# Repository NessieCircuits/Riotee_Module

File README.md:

# Riotee Module Hardware Design Files

The Riotee Module is a stamp-sized unit (27.2mm by 15.2mm) that can be soldered onto a user's \ac{pcb} with additional circuitry like sensors or harvesters to create deployment-ready battery-free devices quickly.
It integrates harvesting circuitry, two MCUs, an RTC, a PCB antenna, and an LED on a compact 4-layer PCB enclosed in a metal RF shield.
The module features breadboard-compatible castellated holes exposing essential signals, including 11 GPIO, two of which can also function as analog inputs.
Four additional signals on the back of the module are available when reflow-soldered onto a carrier board.

For more details and pinouts, refer to the [documentation](https://www.riotee.nessie-circuits.de/docs/latest/hardware/module.html).

Latest design files:
 - [Schematics](https://www.riotee.nessie-circuits.de/artifacts/module/latest/schematics.pdf)
 - [Layout](https://www.riotee.nessie-circuits.de/artifacts/module/latest/pcb.pdf)
 - [3D rendering](https://www.riotee.nessie-circuits.de/artifacts/module/latest/3drendering.png)
 - [Gerber](https://www.riotee.nessie-circuits.de/artifacts/module/latest/gerber.zip)
 - [BOM](https://www.riotee.nessie-circuits.de/artifacts/module/latest/bom.csv)
 - [3D step model](./resources/RioteeModule.step)
 - [Kicad schematic symbol](./resources/RioteeModule.kicad_sym)
 - [Kicad footprint](./resources/RioteeModule.pretty)

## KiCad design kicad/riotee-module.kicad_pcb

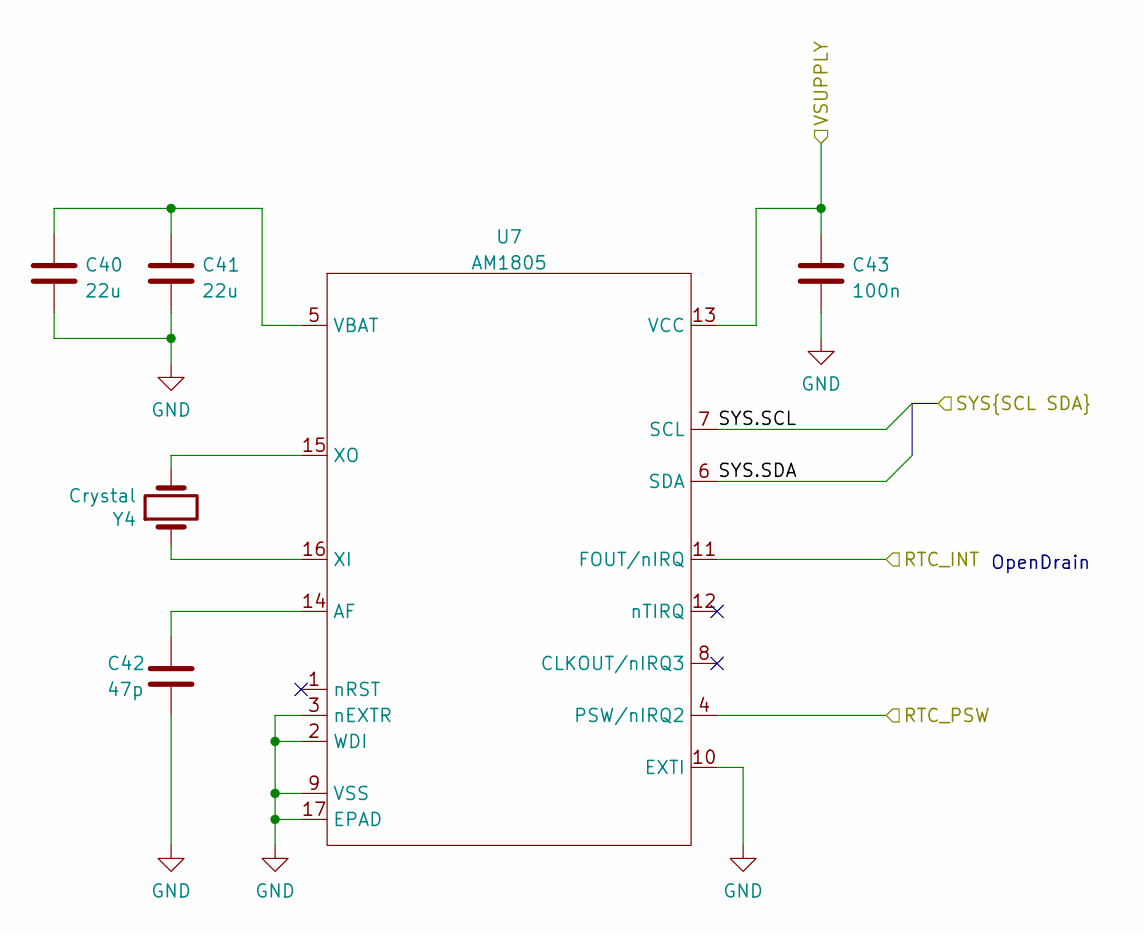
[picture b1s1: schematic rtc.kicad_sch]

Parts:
C40, C41: 22u; C_0402_1005Metric; MPN GRM158R61A226ME15D
C42: 47p; C_0201_0603Metric; MPN CC0201JRNPO9BN470
C43: 100n; C_0201_0603Metric; MPN GRM033R61A104ME15D
U7: AM1805; AM_QFN16; MPN AM1805
Y4: Crystal; ECX-12R; MPN CM8V-T1A-32.768KHZ-9PF-20PPM-TA-QC

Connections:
/Board Connectors/SYS.SCL: U7.7 (SCL); also elsewhere on the board
/Board Connectors/SYS.SDA: U7.6 (SDA); also elsewhere on the board
/Board Connectors/VSHUNT: C43.1, U7.13 (VCC); also elsewhere on the board
/MSP430FR/RTC_INT: U7.11 (FOUT/nIRQ); also elsewhere on the board
/Power Supply/RTC_PSW: U7.4 (PSW/nIRQ2); also elsewhere on the board
GND: C40.2, C41.2, C42.2, C43.2, U7.2 (WDI), U7.3 (nEXTR), U7.9 (VSS), U7.10 (EXTI), U7.17 (EPAD); also elsewhere on the board
unnamed: C42.1, U7.14 (AF)
unnamed: C40.1, C41.1, U7.5 (VBAT)
unnamed: U7.16 (XI), Y4.1
unnamed: U7.15 (XO), Y4.2

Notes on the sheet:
OpenDrain

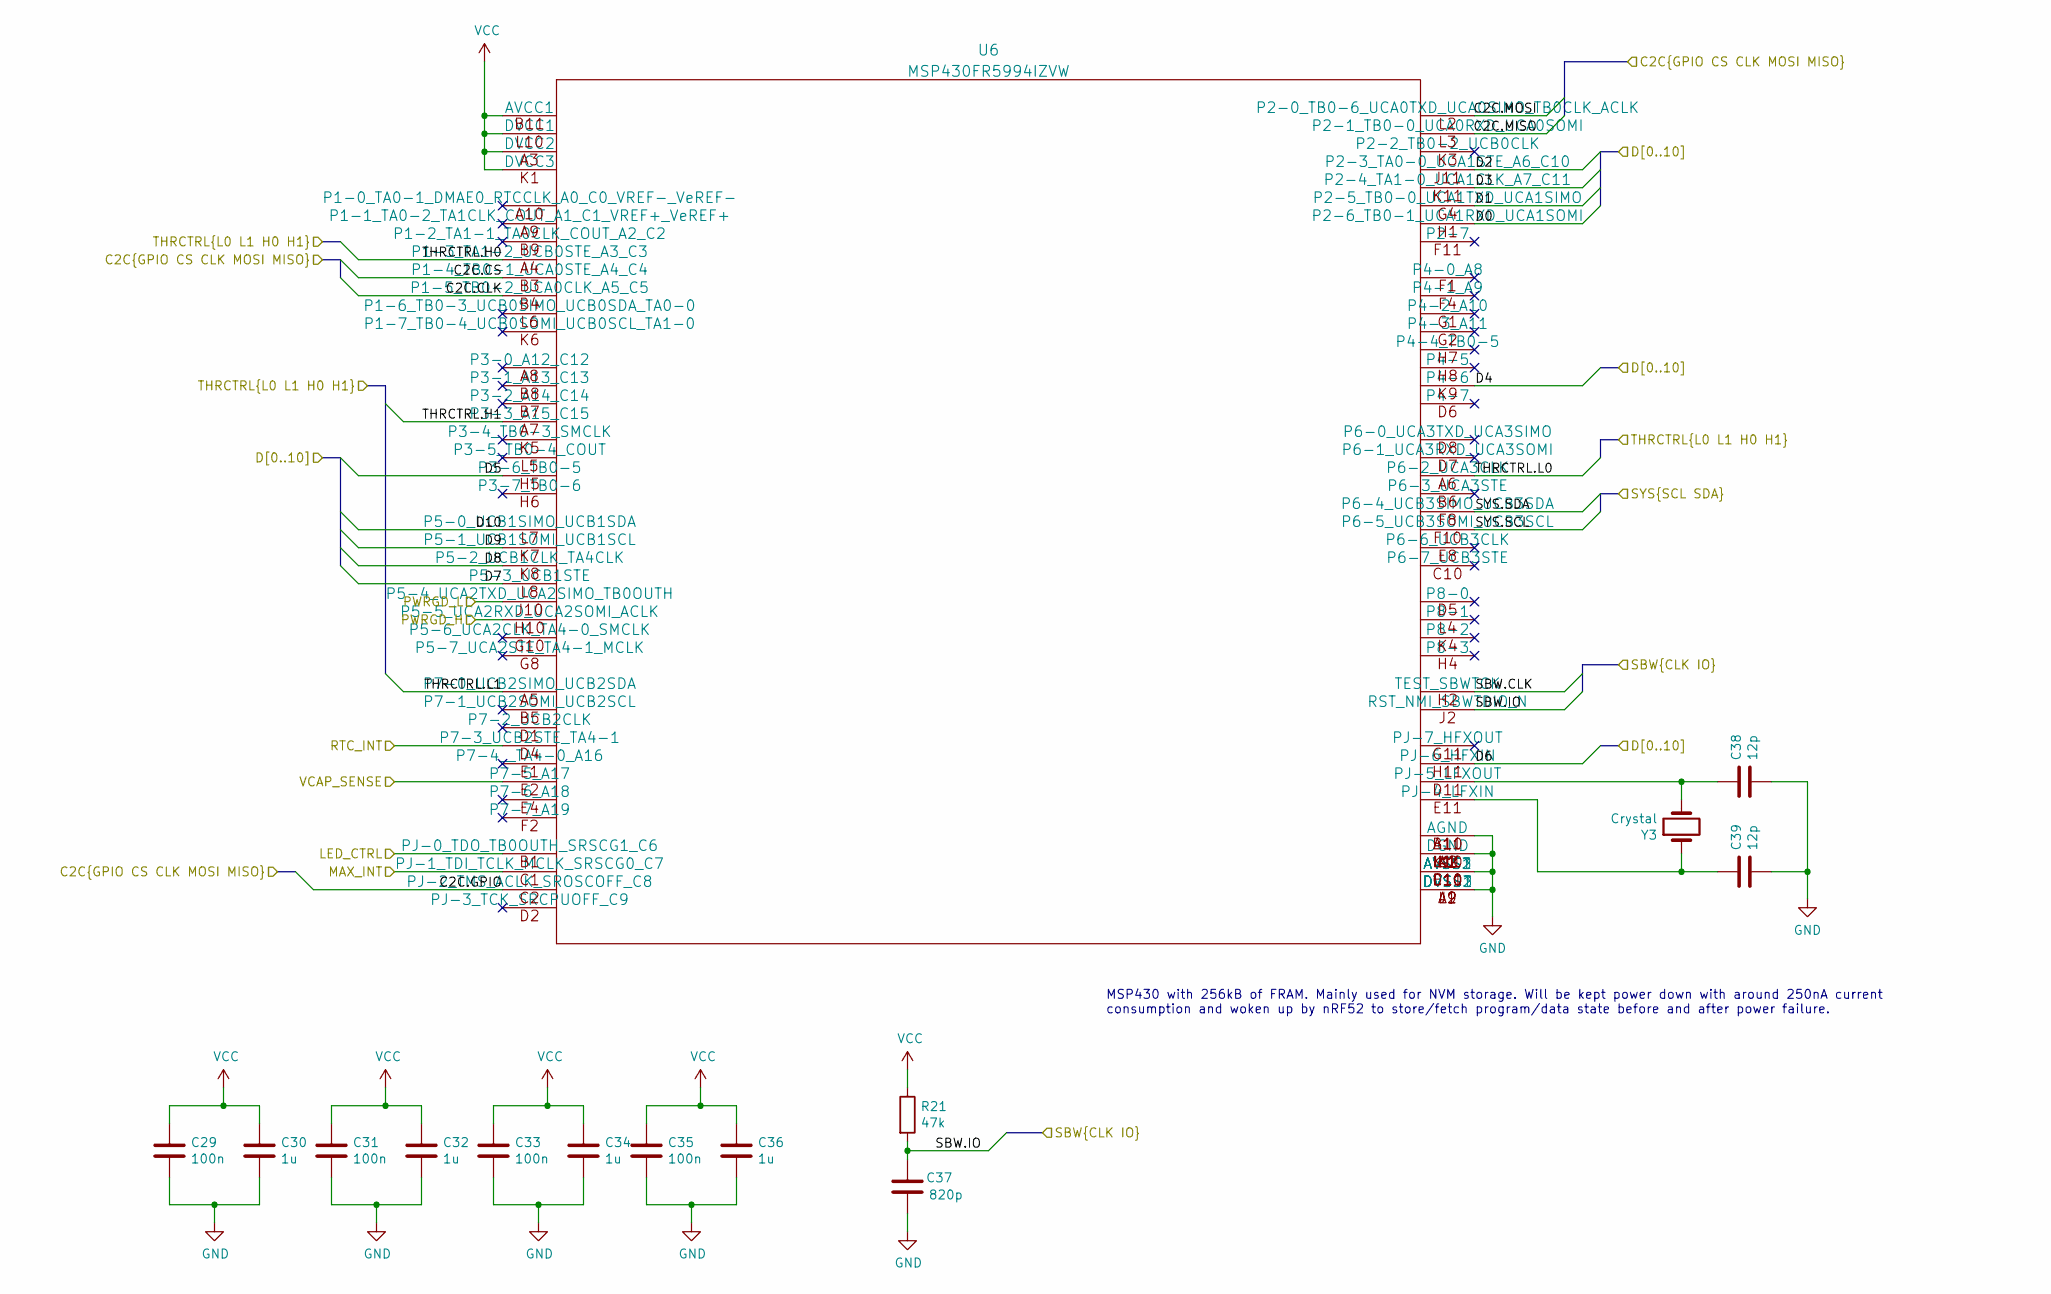
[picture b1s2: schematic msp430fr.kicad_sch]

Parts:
C29, C31, C33, C35: 100n; C_0201_0603Metric; MPN GRM033R61A104ME15D
C30, C32, C34, C36: 1u; C_0201_0603Metric; MPN GRM033R61C105ME15D
C37: 820p; C_0201_0603Metric; MPN GRM0335C1H821JE01D
C38, C39: 12p; C_0201_0603Metric; MPN GRM0335C1H120GA01D
R21: 47k; R_0201_0603Metric; MPN RC0201FR-0747KL
U6: MSP430FR5994IZVW; TI_ZVW; MPN MSP430FR5994IZVW
Y3: Crystal; ECX-12R; MPN CM8V-T1A-32.768KHZ-9PF-20PPM-TA-QC

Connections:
/Board Connectors/D0: U6.H1 (P2-6_TB0-1_UCA1RXD_UCA1SOMI); also elsewhere on the board
/Board Connectors/D1: U6.G4 (P2-5_TB0-0_UCA1TXD_UCA1SIMO); also elsewhere on the board
/Board Connectors/D2: U6.J11 (P2-3_TA0-0_UCA1STE_A6_C10); also elsewhere on the board
/Board Connectors/D3: U6.K11 (P2-4_TA1-0_UCA1CLK_A7_C11); also elsewhere on the board
/Board Connectors/D4: U6.K9 (P4-6); also elsewhere on the board
/Board Connectors/D5: U6.H5 (P3-6_TB0-5); also elsewhere on the board
/Board Connectors/D6: U6.H11 (PJ-6_HFXIN); also elsewhere on the board
/Board Connectors/D7: U6.L8 (P5-3_UCB1STE); also elsewhere on the board
/Board Connectors/D8: U6.K8 (P5-2_UCB1CLK_TA4CLK); also elsewhere on the board
/Board Connectors/D9: U6.K7 (P5-1_UCB1SOMI_UCB1SCL); also elsewhere on the board
/Board Connectors/D10: U6.L7 (P5-0_UCB1SIMO_UCB1SDA); also elsewhere on the board
/Board Connectors/LED_CTRL: U6.B1 (PJ-0_TDO_TB0OUTH_SRSCG1_C6); also elsewhere on the board
/Board Connectors/SBW.CLK: U6.H2 (TEST_SBWTCK); also elsewhere on the board
/Board Connectors/SBW.IO: C37.1, R21.2, U6.J2 (RST_NMI_SBWTDIO_N); also elsewhere on the board
/Board Connectors/SYS.SCL: U6.F10 (P6-5_UCB3SOMI_UCB3SCL); also elsewhere on the board
/Board Connectors/SYS.SDA: U6.F8 (P6-4_UCB3SIMO_UCB3SDA); also elsewhere on the board
/Board Connectors/VCAP_SENSE: U6.E2 (P7-5_A17); also elsewhere on the board
/Energy Management/PWRGD_H: U6.H10 (P5-5_UCA2RXD_UCA2SOMI_ACLK); also elsewhere on the board
/Energy Management/PWRGD_L: U6.J10 (P5-4_UCA2TXD_UCA2SIMO_TB0OUTH); also elsewhere on the board
/Energy Management/THRCTRL.H0: U6.A4 (P1-3_TA1-2_UCB0STE_A3_C3); also elsewhere on the board
/Energy Management/THRCTRL.H1: U6.A7 (P3-3_A15_C15); also elsewhere on the board
/Energy Management/THRCTRL.L0: U6.A6 (P6-2_UCA3CLK); also elsewhere on the board
/Energy Management/THRCTRL.L1: U6.A5 (P7-0_UCB2SIMO_UCB2SDA); also elsewhere on the board
/MSP430FR/C2C.CLK: U6.B4 (P1-5_TB0-2_UCA0CLK_A5_C5); also elsewhere on the board
/MSP430FR/C2C.CS: U6.B3 (P1-4_TB0-1_UCA0STE_A4_C4); also elsewhere on the board
/MSP430FR/C2C.GPIO: U6.C2 (PJ-2_TMS_ACLK_SROSCOFF_C8); also elsewhere on the board
/MSP430FR/C2C.MISO: U6.L3 (P2-1_TB0-0_UCA0RXD_UCA0SOMI); also elsewhere on the board
/MSP430FR/C2C.MOSI: U6.L2 (P2-0_TB0-6_UCA0TXD_UCA0SIMO_TB0CLK_ACLK); also elsewhere on the board
/MSP430FR/MAX_INT: U6.C1 (PJ-1_TDI_TCLK_MCLK_SRSCG0_C7); also elsewhere on the board
/MSP430FR/RTC_INT: U6.D4 (P7-3_UCB2STE_TA4-1); also elsewhere on the board
GND: C29.2, C30.2, C31.2, C32.2, C33.2, C34.2, C35.2, C36.2, C37.2, C38.2, C39.2, U6.A1 (DGND), U6.A2 (DVSS2), U6.A11 (AGND), U6.B10 (AGND), U6.C11 (AVSS1), U6.D10 (AVSS2), U6.E10 (AVSS3), U6.J1 (DVSS3), U6.K2 (DGND), U6.K10 (DGND), U6.L1 (DGND), U6.L9 (DVSS1), U6.L11 (DGND); also elsewhere on the board
unnamed: C39.1, U6.E11 (PJ-4_LFXIN), Y3.1
unnamed: C38.1, U6.D11 (PJ-5_LFXOUT), Y3.2
VCC: C29.1, C30.1, C31.1, C32.1, C33.1, C34.1, C35.1, C36.1, R21.1, U6.A3 (DVCC2), U6.B11 (AVCC1), U6.K1 (DVCC3), U6.L10 (DVCC1); also elsewhere on the board

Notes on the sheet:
MSP430 with 256kB of FRAM. Mainly used for NVM storage. Will be kept power down with around 250nA current consumption and woken up by nRF52 to store/fetch program/data state before and after power failure.

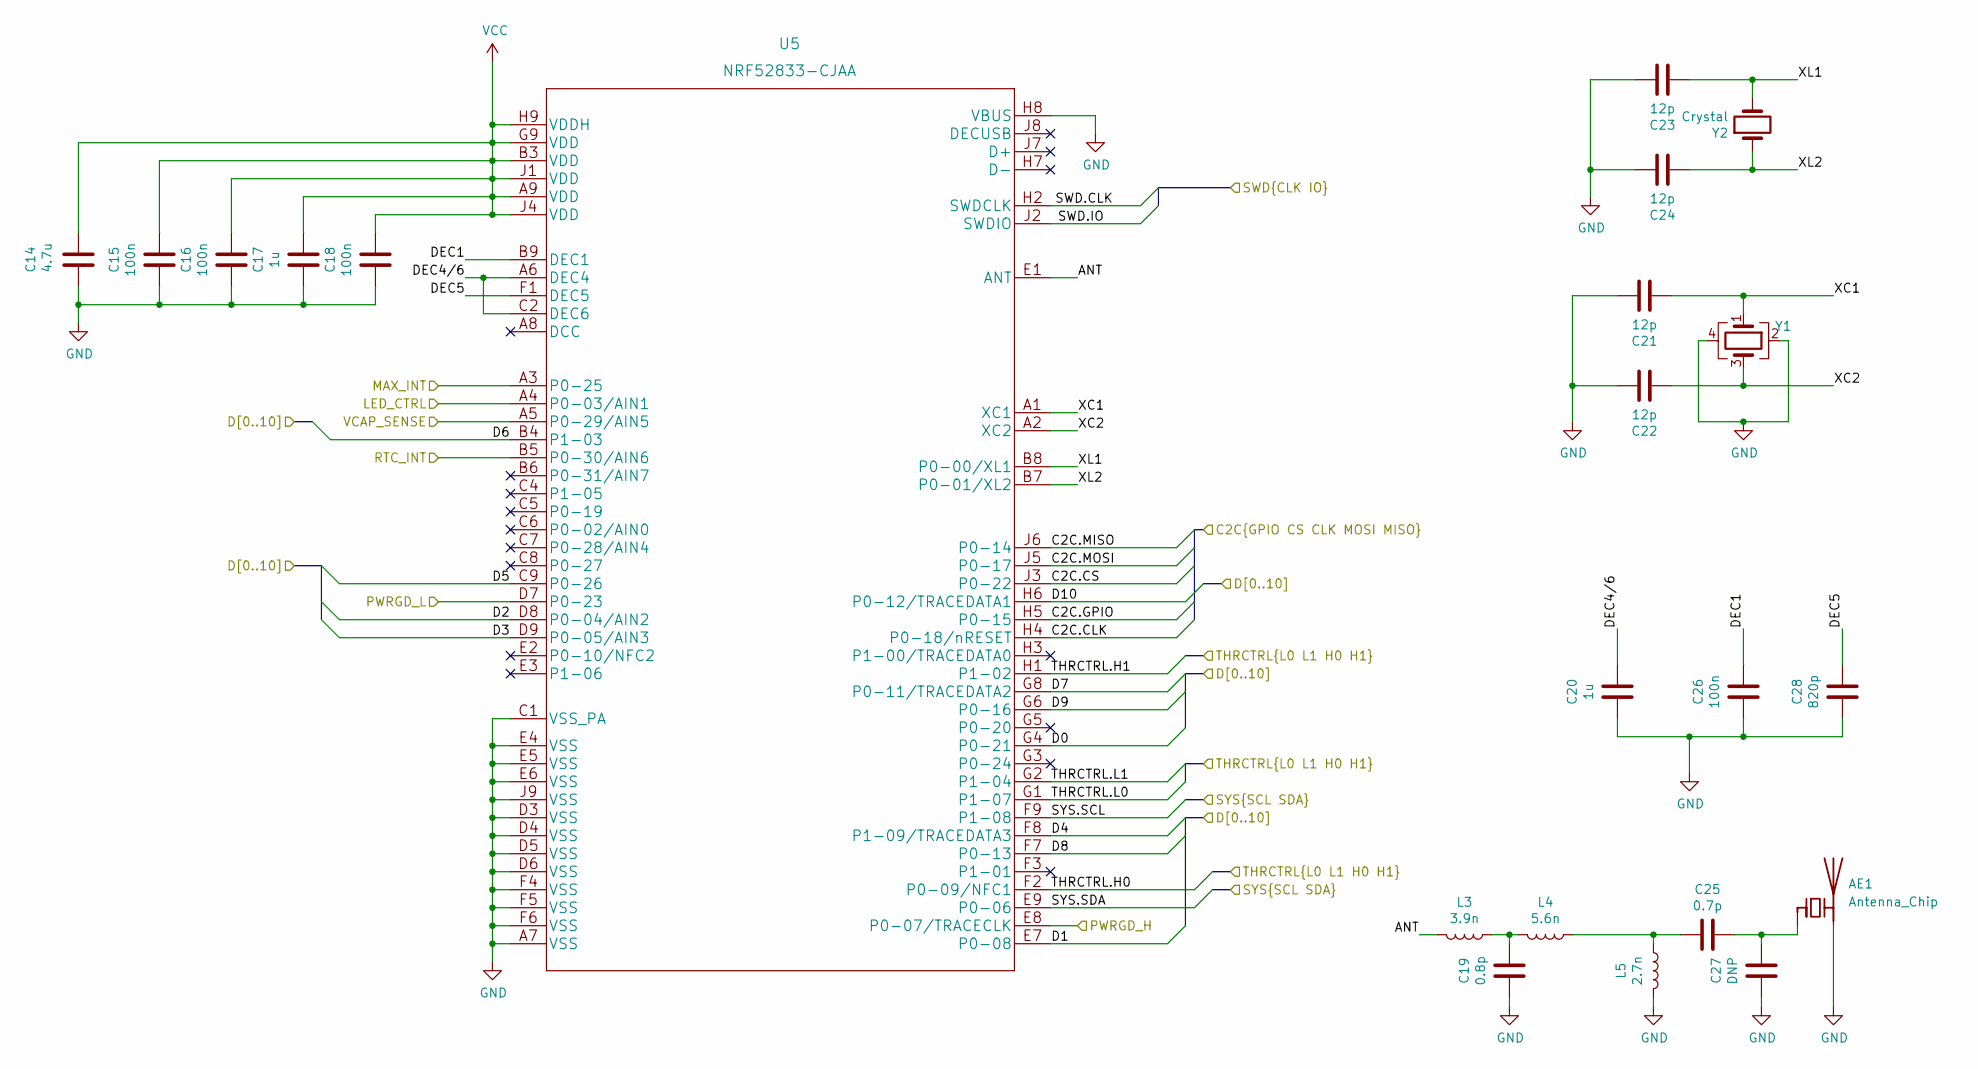
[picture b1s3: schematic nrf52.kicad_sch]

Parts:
AE1: Antenna_Chip; Texas_SWRA117D_2.4GHz_Left
C14: 4.7u; C_0402_1005Metric; MPN CL05A475MP5NRNC
C15, C16, C18, C26: 100n; C_0201_0603Metric; MPN GRM033R61A104ME15D
C17, C20: 1u; C_0201_0603Metric; MPN GRM033R61C105ME15D
C19: 0.8p; RFSMD_0201_0603Metric; MPN GRT0335C1HR80WA02D
C21, C22, C23, C24: 12p; C_0201_0603Metric; MPN GRM0335C1H120GA01D
C25: 0.7p; RFSMD_0201_0603Metric; MPN GRM0335C1HR70WA01D
C27: DNP; RFSMD_0201_0603Metric
C28: 820p; C_0201_0603Metric; MPN GRM0335C1H821JE01D
L3: 3.9n; RFSMD_0201_0603Metric; MPN LQP03TN3N9B02D
L4: 5.6n; RFSMD_0201_0603Metric; MPN LQP03TN5N6J02D
L5: 2.7n; RFSMD_0201_0603Metric; MPN LQP03TN2N7B02D
U5: NRF52833-CJAA; MPN NRF52833-CJAA
Y1: ECS-320-8-47B-7KM-TR; ECS_ECX-1247B; MPN ECS-320-CDX-2152
Y2: Crystal; ECX-12R; MPN CM8V-T1A-32.768KHZ-9PF-20PPM-TA-QC

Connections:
/Board Connectors/D0: U5.G4 (P0-21); also elsewhere on the board
/Board Connectors/D1: U5.E7 (P0-08); also elsewhere on the board
/Board Connectors/D2: U5.D8 (P0-04/AIN2); also elsewhere on the board
/Board Connectors/D3: U5.D9 (P0-05/AIN3); also elsewhere on the board
/Board Connectors/D4: U5.F8 (P1-09/TRACEDATA3); also elsewhere on the board
/Board Connectors/D5: U5.C9 (P0-26); also elsewhere on the board
/Board Connectors/D6: U5.B4 (P1-03); also elsewhere on the board
/Board Connectors/D7: U5.G8 (P0-11/TRACEDATA2); also elsewhere on the board
/Board Connectors/D8: U5.F7 (P0-13); also elsewhere on the board
/Board Connectors/D9: U5.G6 (P0-16); also elsewhere on the board
/Board Connectors/D10: U5.H6 (P0-12/TRACEDATA1); also elsewhere on the board
/Board Connectors/LED_CTRL: U5.A4 (P0-03/AIN1); also elsewhere on the board
/Board Connectors/SWD.CLK: U5.H2 (SWDCLK); also elsewhere on the board
/Board Connectors/SWD.IO: U5.J2 (SWDIO); also elsewhere on the board
/Board Connectors/SYS.SCL: U5.F9 (P1-08); also elsewhere on the board
/Board Connectors/SYS.SDA: U5.E9 (P0-06); also elsewhere on the board
/Board Connectors/VCAP_SENSE: U5.A5 (P0-29/AIN5); also elsewhere on the board
/Energy Management/PWRGD_H: U5.E8 (P0-07/TRACECLK); also elsewhere on the board
/Energy Management/PWRGD_L: U5.D7 (P0-23); also elsewhere on the board
/Energy Management/THRCTRL.H0: U5.F2 (P0-09/NFC1); also elsewhere on the board
/Energy Management/THRCTRL.H1: U5.H1 (P1-02); also elsewhere on the board
/Energy Management/THRCTRL.L0: U5.G1 (P1-07); also elsewhere on the board
/Energy Management/THRCTRL.L1: U5.G2 (P1-04); also elsewhere on the board
/MSP430FR/C2C.CLK: U5.H4 (P0-18/nRESET); also elsewhere on the board
/MSP430FR/C2C.CS: U5.J3 (P0-22); also elsewhere on the board
/MSP430FR/C2C.GPIO: U5.H5 (P0-15); also elsewhere on the board
/MSP430FR/C2C.MISO: U5.J6 (P0-14); also elsewhere on the board
/MSP430FR/C2C.MOSI: U5.J5 (P0-17); also elsewhere on the board
/MSP430FR/MAX_INT: U5.A3 (P0-25); also elsewhere on the board
/MSP430FR/RTC_INT: U5.B5 (P0-30/AIN6); also elsewhere on the board
/nRF52/ANT: L3.2, U5.E1 (ANT)
/nRF52/DEC1: C26.2, U5.B9 (DEC1)
/nRF52/DEC4/6: C20.2, U5.A6 (DEC4), U5.C2 (DEC6)
/nRF52/DEC5: C28.2, U5.F1 (DEC5)
/nRF52/XC1: C21.1, U5.A1 (XC1), Y1.1
/nRF52/XC2: C22.1, U5.A2 (XC2), Y1.3
/nRF52/XL1: C23.1, U5.B8 (P0-00/XL1), Y2.2
/nRF52/XL2: C24.1, U5.B7 (P0-01/XL2), Y2.1
GND: AE1.2 (PCB_Trace), C14.2, C15.1, C16.1, C17.1, C18.1, C19.1, C20.1, C21.2, C22.2, C23.2, C24.2, C26.1, C27.1, C28.1, L5.2, U5.A7 (VSS), U5.C1 (VSS_PA), U5.D3 (VSS), U5.D4 (VSS), U5.D5 (VSS), U5.D6 (VSS), U5.E4 (VSS), U5.E5 (VSS), U5.E6 (VSS), U5.F4 (VSS), U5.F5 (VSS), U5.F6 (VSS), U5.H8 (VBUS), U5.J9 (VSS), Y1.2, Y1.4; also elsewhere on the board
unnamed: AE1.1 (FEED), C25.2, C27.2
unnamed: C19.2, L3.1, L4.2
unnamed: C25.1, L4.1, L5.1
VCC: C14.1, C15.2, C16.2, C17.2, C18.2, U5.A9 (VDD), U5.B3 (VDD), U5.G9 (VDD), U5.H9 (VDDH), U5.J1 (VDD), U5.J4 (VDD); also elsewhere on the board

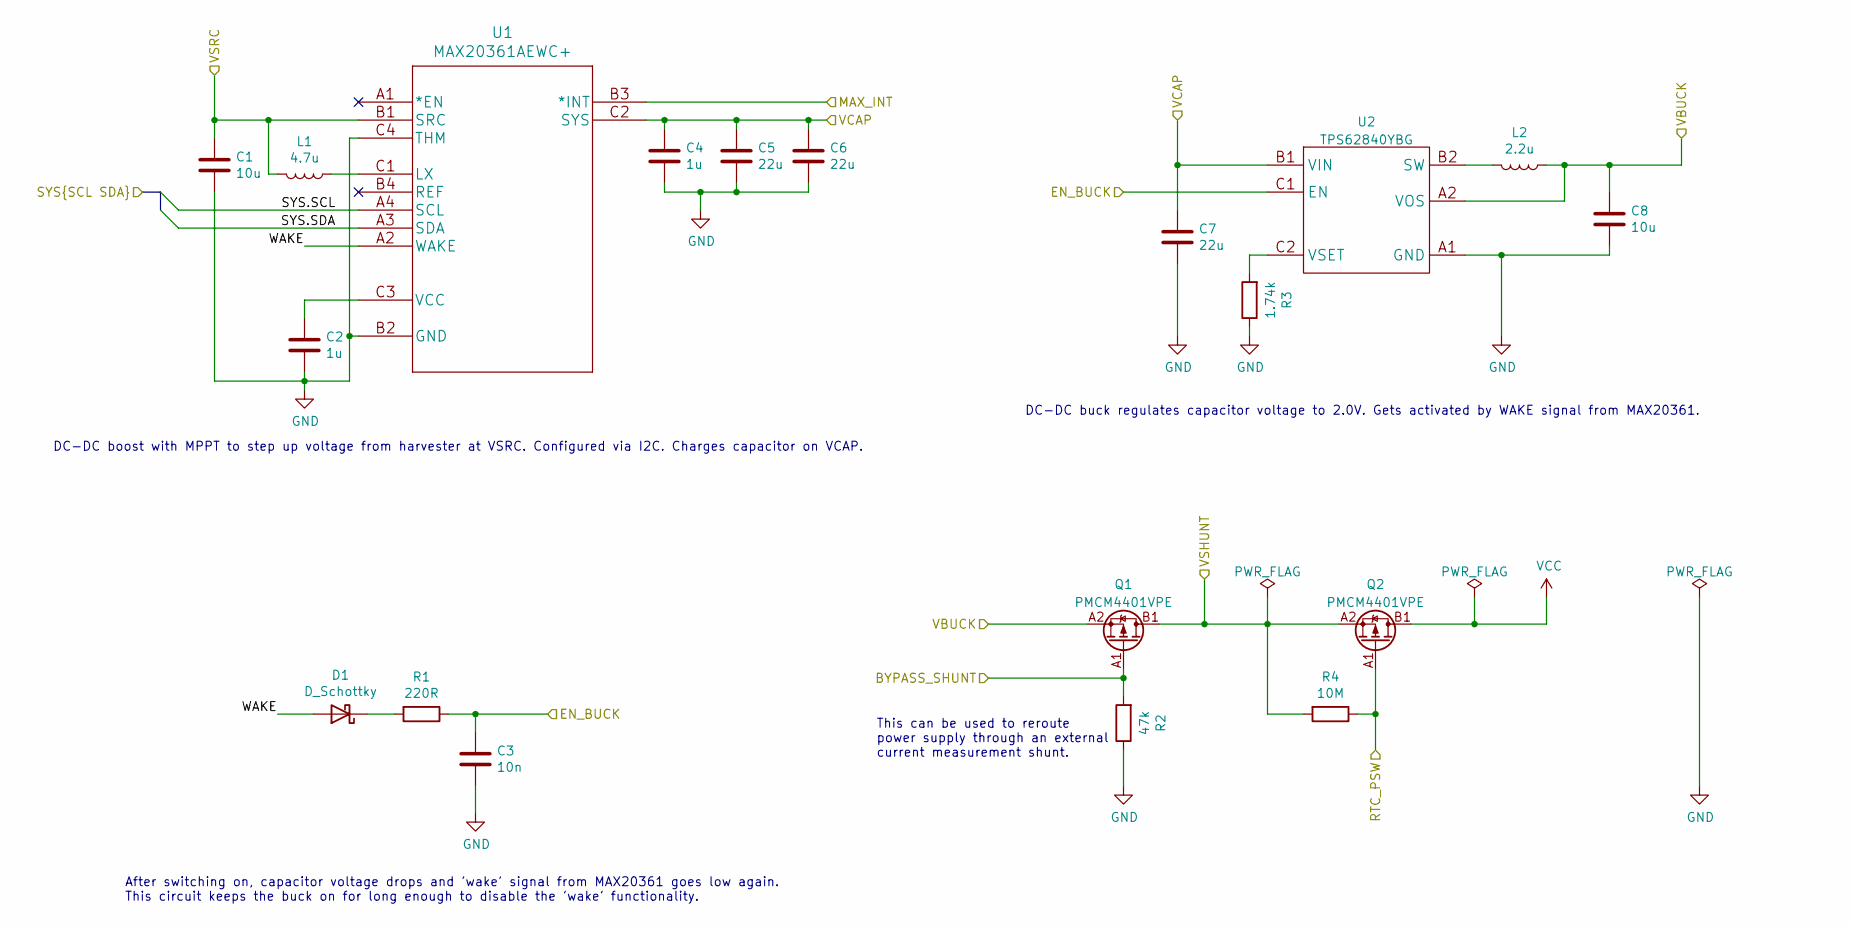
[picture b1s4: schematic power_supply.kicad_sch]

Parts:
C1, C8: 10u; C_0402_1005Metric; MPN GRM155R61A106ME11D
C2, C4: 1u; C_0201_0603Metric; MPN GRM033R61C105ME15D
C3: 10n; C_0201_0603Metric; MPN GRM033R61A103KA01D
C5, C6, C7: 22u; C_0402_1005Metric; MPN GRM158R61A226ME15D
D1: D_Schottky; D_0402_1005Metric; MPN CDBQR0130R
L1: 4.7u; L_0805_2012Metric; MPN MLZ2012N4R7LTD25
L2: 2.2u; L_0603_1608Metric; MPN MLZ1608N2R2LT000
Q1, Q2: PMCM4401VPE; NXP_WLCSP4; MPN PMCM4401VPEZ
R1: 220R; R_0201_0603Metric; MPN RC0201FR-07220RL
R2: 47k; R_0201_0603Metric; MPN RC0201FR-0747KL
R3: 1.74k; R_0201_0603Metric; MPN RC0201FR-071K74L
R4: 10M; R_0201_0603Metric; MPN RC0201FR-0710ML
U1: MAX20361AEWC+; MX_W121C1+2; MPN MAX20361AEWC+
U2: TPS62840YBG; TI_YBG6; MPN TPS62840YBG

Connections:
/Board Connectors/BYPASS_SHUNT: Q1.A1 (G), R2.2; also elsewhere on the board
/Board Connectors/EN_BUCK: C3.1, R1.1, U2.C1 (EN); also elsewhere on the board
/Board Connectors/SYS.SCL: U1.A4 (SCL); also elsewhere on the board
/Board Connectors/SYS.SDA: U1.A3 (SDA); also elsewhere on the board
/Board Connectors/VBUCK: C8.1, L2.1, Q1.A2 (S), U2.A2 (VOS); also elsewhere on the board
/Board Connectors/VCAP: C4.1, C5.1, C6.1, C7.1, U1.C2 (SYS), U2.B1 (VIN); also elsewhere on the board
/Board Connectors/VSHUNT: Q1.B1 (D), Q2.A2 (S), R4.2; also elsewhere on the board
/Board Connectors/VSRC: C1.1, L1.2, U1.B1 (SRC); also elsewhere on the board
/MSP430FR/MAX_INT: U1.B3 (*INT); also elsewhere on the board
/Power Supply/RTC_PSW: Q2.A1 (G), R4.1; also elsewhere on the board
/Power Supply/WAKE: D1.2 (A), U1.A2 (WAKE)
GND: C1.2, C2.2, C3.2, C4.2, C5.2, C6.2, C7.2, C8.2, R2.1, R3.1, U1.B2 (GND), U1.C4 (THM), U2.A1 (GND); also elsewhere on the board
unnamed: D1.1 (K), R1.2
unnamed: L1.1, U1.C1 (LX)
unnamed: C2.1, U1.C3 (VCC)
unnamed: L2.2, U2.B2 (SW)
unnamed: R3.2, U2.C2 (VSET)
VCC: Q2.B1 (D); also elsewhere on the board

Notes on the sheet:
After switching on, capacitor voltage drops and 'wake' signal from MAX20361 goes low again. This circuit keeps the buck on for long enough to disable the 'wake' functionality.
This can be used to reroute power supply through an external current measurement shunt.
DC-DC boost with MPPT to step up voltage from harvester at VSRC. Configured via I2C. Charges capacitor on VCAP.
DC-DC buck regulates capacitor voltage to 2.0V. Gets activated by WAKE signal from MAX20361.

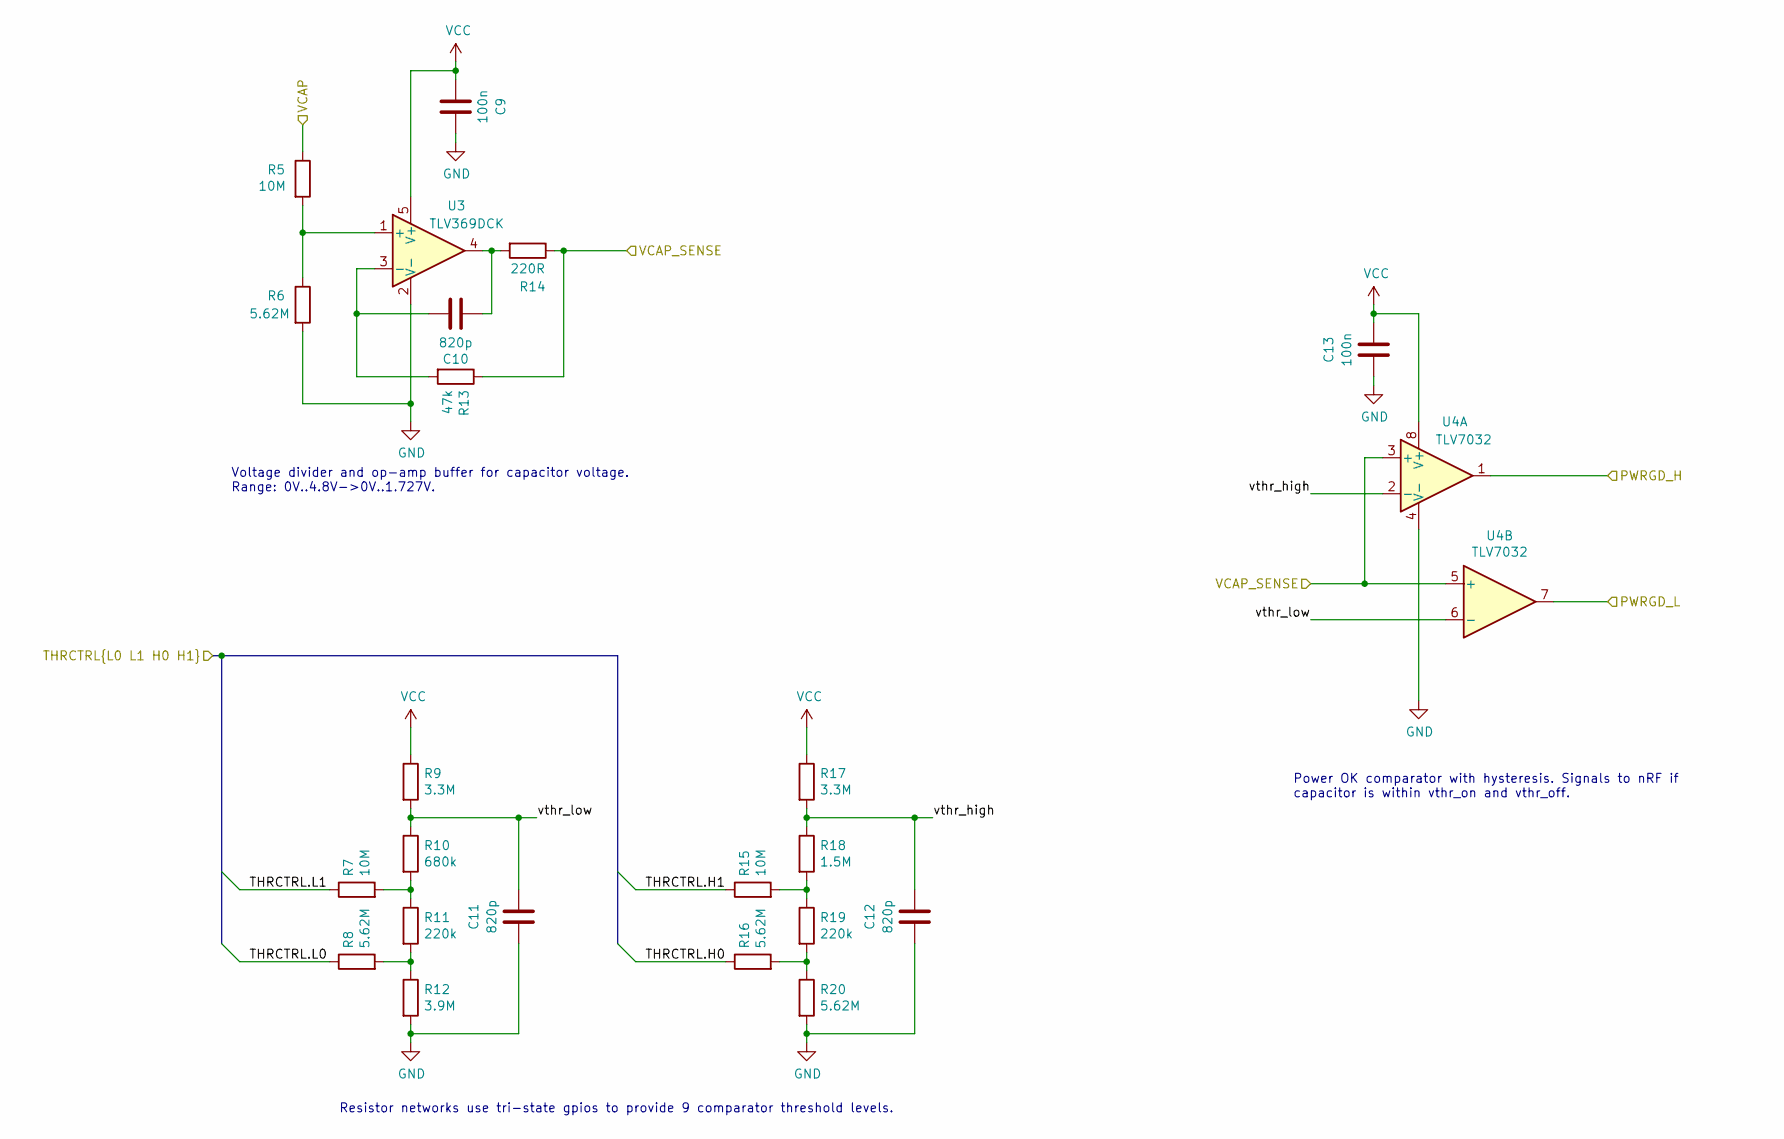
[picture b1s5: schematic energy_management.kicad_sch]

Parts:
C9, C13: 100n; C_0201_0603Metric; MPN GRM033R61A104ME15D
C10, C11, C12: 820p; C_0201_0603Metric; MPN GRM0335C1H821JE01D
R5, R7, R15: 10M; R_0201_0603Metric; MPN RC0201FR-0710ML
R6, R8, R16, R20: 5.62M; R_0201_0603Metric; MPN RC0201FR-075M62L
R9, R17: 3.3M; R_0201_0603Metric; MPN RC0201FR-073M3L
R10: 680k; R_0201_0603Metric; MPN RC0201FR-07680KL
R11, R19: 220k; R_0201_0603Metric; MPN RC0201FR-07220KL
R12: 3.9M; R_0201_0603Metric; MPN RC0201FR-073M9L
R13: 47k; R_0201_0603Metric; MPN RC0201FR-0747KL
R14: 220R; R_0201_0603Metric; MPN RC0201FR-07220RL
R18: 1.5M; R_0201_0603Metric; MPN RC0201FR-071M5L
U3: TLV369DCK; TI_SC70-5_DCK5; MPN TLV369IDCK
U4: TLV7032; TI_WSON8_DSG; MPN TLV7032DSG

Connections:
/Board Connectors/VCAP: R5.1; also elsewhere on the board
/Board Connectors/VCAP_SENSE: R13.1, R14.1, U4.3 (+), U4.5 (+); also elsewhere on the board
/Energy Management/PWRGD_H: U4.1; also elsewhere on the board
/Energy Management/PWRGD_L: U4.7; also elsewhere on the board
/Energy Management/THRCTRL.H0: R16.1; also elsewhere on the board
/Energy Management/THRCTRL.H1: R15.1; also elsewhere on the board
/Energy Management/THRCTRL.L0: R8.1; also elsewhere on the board
/Energy Management/THRCTRL.L1: R7.1; also elsewhere on the board
/Energy Management/vthr_high: C12.2, R17.2, R18.1, U4.2 (-)
/Energy Management/vthr_low: C11.2, R9.2, R10.1, U4.6 (-)
GND: C9.1, C11.1, C12.1, C13.1, R6.2, R12.2, R20.2, U3.2 (V-), U4.4 (V-), U4.9 (THM); also elsewhere on the board
unnamed: C10.1, R14.2, U3.4
unnamed: R7.2, R10.2, R11.1
unnamed: R8.2, R11.2, R12.1
unnamed: R15.2, R18.2, R19.1
unnamed: R16.2, R19.2, R20.1
unnamed: R5.2, R6.1, U3.1 (+)
unnamed: C10.2, R13.2, U3.3 (-)
VCC: C9.2, C13.2, R9.1, R17.1, U3.5 (V+), U4.8 (V+); also elsewhere on the board

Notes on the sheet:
Power OK comparator with hysteresis. Signals to nRF if capacitor is within vthr_on and vthr_off.
Resistor networks use tri-state gpios to provide 9 comparator threshold levels.
Voltage divider and op-amp buffer for capacitor voltage. Range: 0V..4.8V->0V..1.727V.

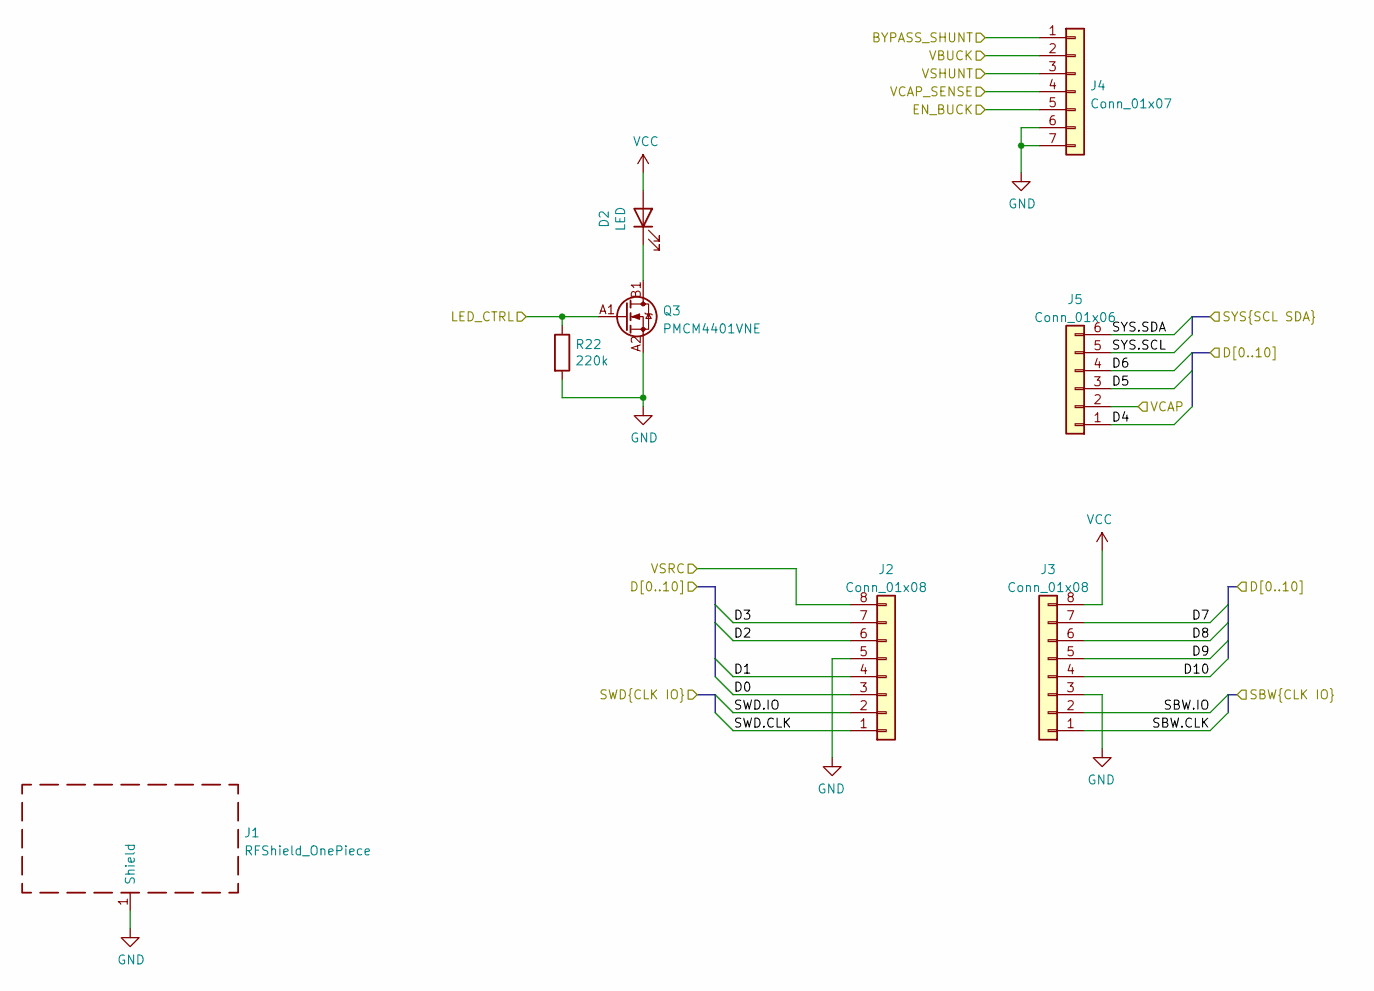
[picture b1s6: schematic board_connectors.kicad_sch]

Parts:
D2: LED; LED_0402_1005Metric; MPN 5988A20107F
J1: RFShield_OnePiece; EMI_SHIELD_CSTM
J2: Conn_01x08; CastellatedHoles_1x08_P2.54mm_Left
J3: Conn_01x08; CastellatedHoles_1x08_P2.54mm_Right
J4: Conn_01x07; BackPads
J5: Conn_01x06; CastellatedHoles_1x06_P2.54mm
Q3: PMCM4401VNE; NXP_WLCSP4; MPN PMCM4401VNEAZ
R22: 220k; R_0201_0603Metric; MPN RC0201FR-07220KL

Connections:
/Board Connectors/BYPASS_SHUNT: J4.1; also elsewhere on the board
/Board Connectors/D0: J2.3; also elsewhere on the board
/Board Connectors/D1: J2.4; also elsewhere on the board
/Board Connectors/D2: J2.6; also elsewhere on the board
/Board Connectors/D3: J2.7; also elsewhere on the board
/Board Connectors/D4: J5.1; also elsewhere on the board
/Board Connectors/D5: J5.3; also elsewhere on the board
/Board Connectors/D6: J5.4; also elsewhere on the board
/Board Connectors/D7: J3.7; also elsewhere on the board
/Board Connectors/D8: J3.6; also elsewhere on the board
/Board Connectors/D9: J3.5; also elsewhere on the board
/Board Connectors/D10: J3.4; also elsewhere on the board
/Board Connectors/EN_BUCK: J4.5; also elsewhere on the board
/Board Connectors/LED_CTRL: Q3.A1 (G), R22.1; also elsewhere on the board
/Board Connectors/SBW.CLK: J3.1; also elsewhere on the board
/Board Connectors/SBW.IO: J3.2; also elsewhere on the board
/Board Connectors/SWD.CLK: J2.1; also elsewhere on the board
/Board Connectors/SWD.IO: J2.2; also elsewhere on the board
/Board Connectors/SYS.SCL: J5.5; also elsewhere on the board
/Board Connectors/SYS.SDA: J5.6; also elsewhere on the board
/Board Connectors/VBUCK: J4.2; also elsewhere on the board
/Board Connectors/VCAP: J5.2; also elsewhere on the board
/Board Connectors/VCAP_SENSE: J4.4; also elsewhere on the board
/Board Connectors/VSHUNT: J4.3; also elsewhere on the board
/Board Connectors/VSRC: J2.8; also elsewhere on the board
GND: J1.1 (Shield), J2.5, J3.3, J4.6, J4.7, Q3.A2 (S), R22.2; also elsewhere on the board
unnamed: D2.1 (K), Q3.B1 (D)
VCC: D2.2 (A), J3.8; also elsewhere on the board

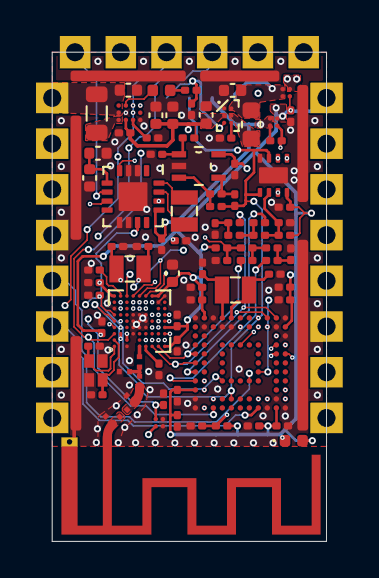
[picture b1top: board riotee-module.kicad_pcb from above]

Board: 4 copper layers, 15.2 x 27.2 mm, 92 parts (1 on the bottom side), 74 nets.

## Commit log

2023-08-21 update Riotee Module 3d model
2024-10-15 generate bom and gerber in github workflow with kibot
2024-11-14 add 3d model of 0402 diode
2024-11-14 auto update schematics
